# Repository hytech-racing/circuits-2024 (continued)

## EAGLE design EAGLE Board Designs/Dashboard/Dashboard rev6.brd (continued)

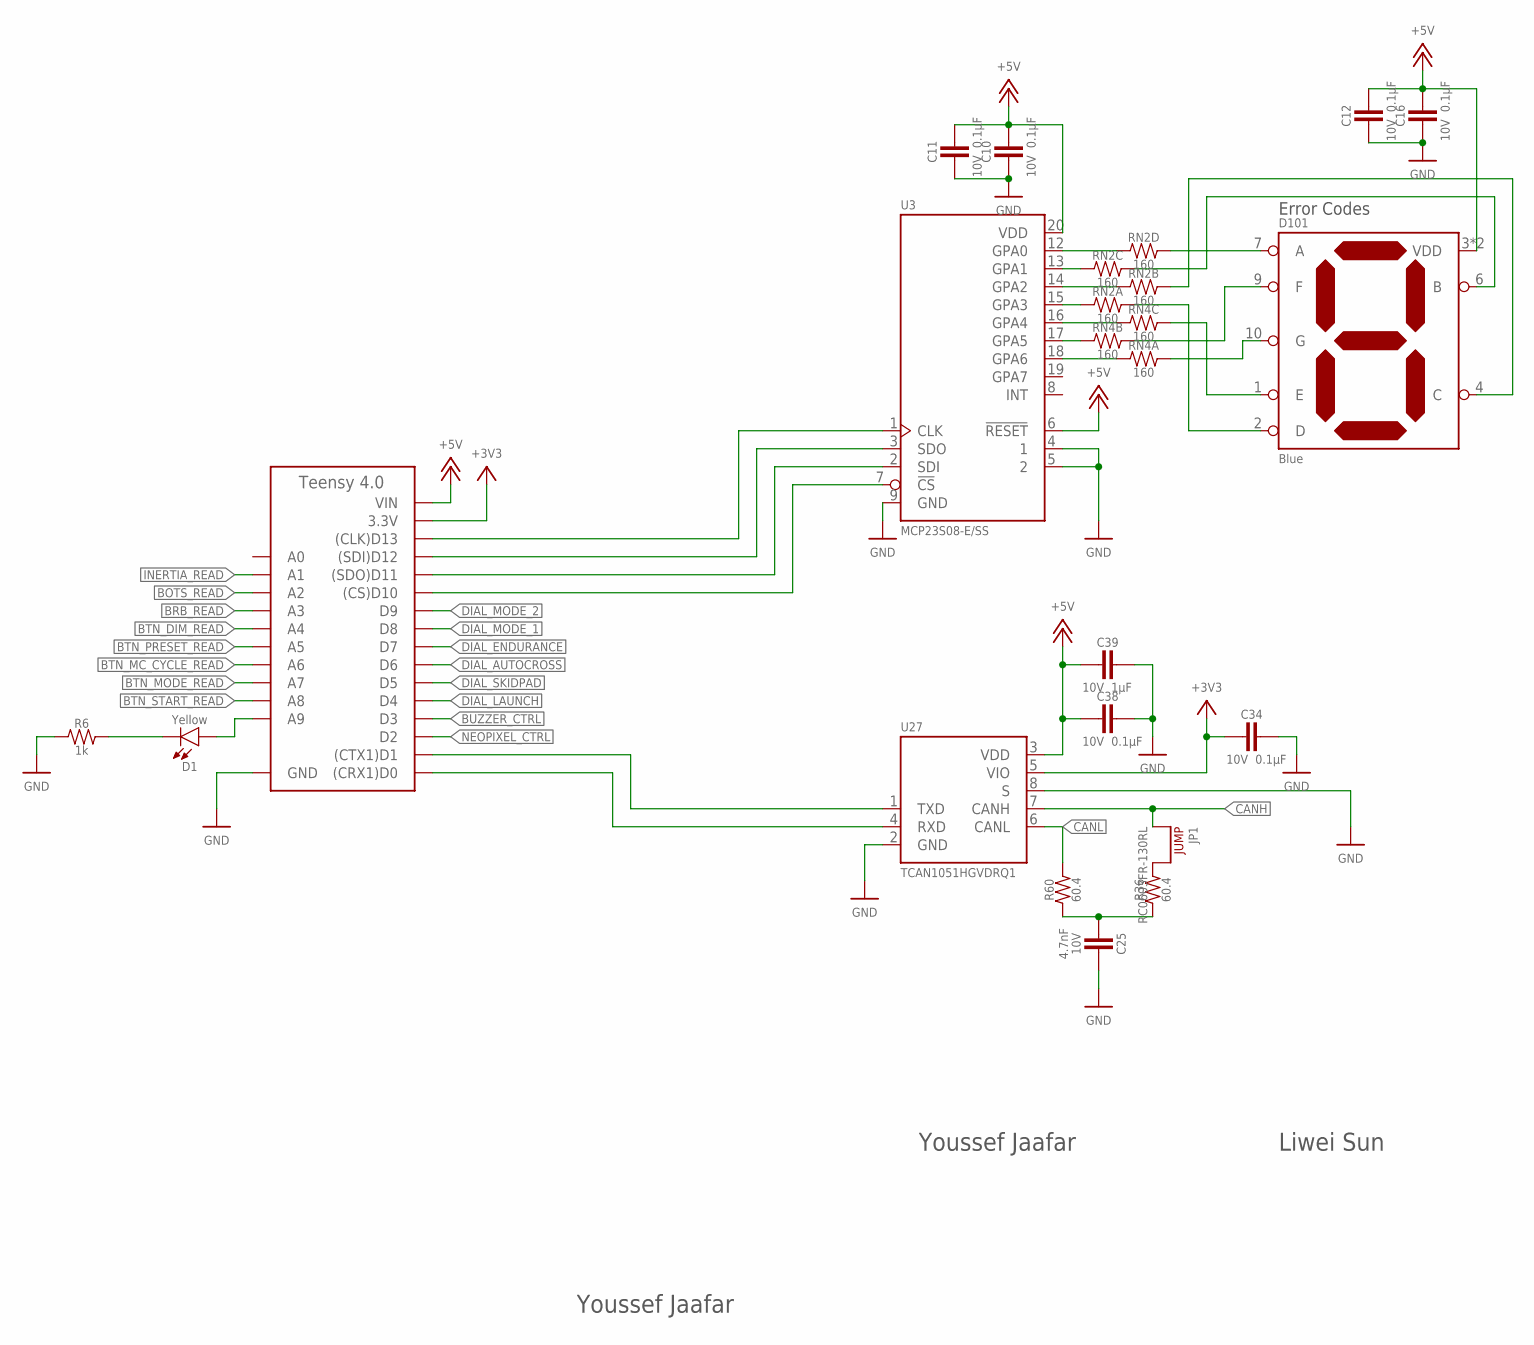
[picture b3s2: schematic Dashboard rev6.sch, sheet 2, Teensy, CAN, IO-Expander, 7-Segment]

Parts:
A2: TEENSY_4.0SM; TEENSY_SHORT_SSM
C10, C11, C12, C16, C34, C38: CAPACITOR_0603_10V_0.1UF; 0603-CAP
C25: CAPACITOR_0603_10V_4.7NF; 0603-CAP
C39: CAPACITOR_0603_10V_1UF; 0603-CAP
D1: LED_0603_YELLOW; 0603-LED
D101: LED_7_SEGMENT_BLUE_DSM7TA; DSM7T
JP1: JUMPER_0603_; 0603-RES
R6: RESISTOR_0603_1K; 0603-RES
R36, R60: RESISTOR_0603_60.4; 0603-RES
RN2, RN4: RESISTOR_NETWORK_4_160; 1206-RES-ARRAY
U3: MCP23S08; SSOP-20
U27: TCAN1051HQV-Q1; SOIC-08(NARROW,0.15")

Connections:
+3V3: A2.3.3V, C34.2, U27.5 (VIO); also elsewhere on the board
+5V: A2.VIN, C10.1, C11.1, C12.1, C16.1, C38.2, C39.2, D101.3 (VDD), D101.8 (VDD), U3.6 (!RESET), U3.20 (VDD), U27.3 (VDD); also elsewhere on the board
A: D101.7 (A), RN2.5 (2)
A2: RN2.4 (1), U3.12 (GPA0)
B: D101.6 (B), RN2.6 (2)
B2: RN2.3 (1), U3.13 (GPA1)
BOTS_READ: A2.D16 (A2); also elsewhere on the board
BRB_READ: A2.D17 (A3); also elsewhere on the board
BTN_DIM_READ: A2.D18 (A4); also elsewhere on the board
BTN_MC_CYCLE_READ: A2.D20 (A6); also elsewhere on the board
BTN_MODE_READ: A2.D21 (A7); also elsewhere on the board
BTN_PRESET_READ: A2.D19 (A5); also elsewhere on the board
BTN_START_READ: A2.D22 (A8); also elsewhere on the board
BUZZER_CTRL: A2.D3; also elsewhere on the board
C: D101.4 (C), RN2.7 (2)
C2: RN2.2 (1), U3.14 (GPA2)
CANH: JP1.1, U27.7 (CANH); also elsewhere on the board
CANL: R60.2, U27.6 (CANL); also elsewhere on the board
CIPO: A2.D12 ((SDI)D12), U3.3 (SDO)
CLK: A2.D13 ((CLK)D13), U3.1 (CLK)
COPI: A2.D11 ((SDO)D11), U3.2 (SDI)
CRX: A2.D0 ((CRX1)D0), U27.4 (RXD)
CS_CAN: A2.D10 ((CS)D10), U3.7 (!CS)
CTX: A2.D1 ((CTX1)D1), U27.1 (TXD)
D: D101.2 (D), RN2.8 (2)
D2: RN2.1, U3.15 (GPA3)
DIAL_AUTOCROSS: A2.D6; also elsewhere on the board
DIAL_ENDURANCE: A2.D7; also elsewhere on the board
DIAL_LAUNCH: A2.D4; also elsewhere on the board
DIAL_MODE_1: A2.D8; also elsewhere on the board
DIAL_MODE_2: A2.D9; also elsewhere on the board
DIAL_SKIDPAD: A2.D5; also elsewhere on the board
E: D101.1 (E), RN4.6 (2)
E2: RN4.3 (1), U3.16 (GPA4)
F: D101.9 (F), RN4.7 (2)
F2: RN4.2 (1), U3.17 (GPA5)
G: D101.10 (G), RN4.8 (2)
G2: RN4.1, U3.18 (GPA6)
GND: A2.AGND/GND (GND), A2.GND, C10.2, C11.2, C12.2, C16.2, C25.1, C34.1, C38.1, C39.1, R6.1, U3.4 (1), U3.5 (2), U3.9 (GND), U27.2 (GND), U27.8 (S); also elsewhere on the board
INERTIA_READ: A2.D15 (A1); also elsewhere on the board
unnamed: D1.1 (C), R6.2
unnamed: JP1.2, R36.2
unnamed: C25.2, R36.1, R60.1
NEOPIXEL_CTRL: A2.D2; also elsewhere on the board
TEENSY_ON: A2.D23 (A9), D1.2 (A)

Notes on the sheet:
Youssef Jaafar
Error Codes
Liwei Sun

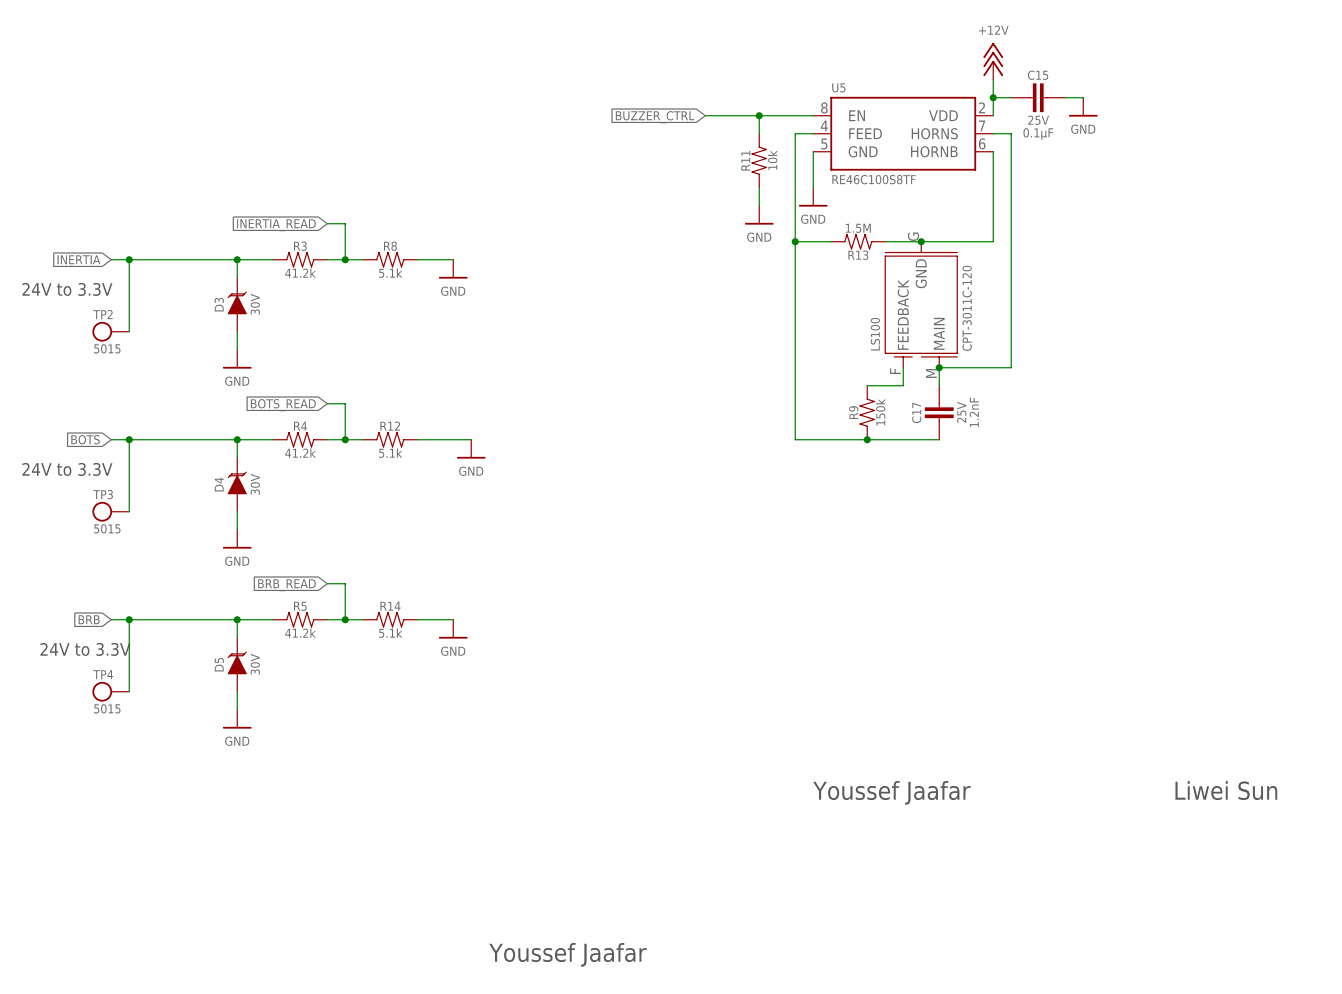
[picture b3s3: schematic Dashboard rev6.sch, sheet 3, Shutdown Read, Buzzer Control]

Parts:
C15: CAPACITOR_0603_25V_0.1UF; 0603-CAP
C17: CAPACITOR_0603_25V_1.2NF; 0603-CAP
D3, D4, D5: TVS_DO-214AA_30V; DO-214AA
LS100: BUZZER_3_PIN_CPT-3011C-120; CPT-3011C-120
R3, R4, R5: RESISTOR_0603_41.2K; 0603-RES
R8, R12, R14: RESISTOR_0603_5.1K; 0603-RES
R9: RESISTOR_0603_150K; 0603-RES
R11: RESISTOR_0603_10K; 0603-RES
R13: RESISTOR_0603_1.5M; 0603-RES
TP2, TP3, TP4: TEST_POINT; 5015
U5: RE46C100; SOIC-08(NARROW,0.15")

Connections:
+12V: C15.2, U5.2 (VDD); also elsewhere on the board
BOTS: D4.2 (C), R4.1, TP3.1; also elsewhere on the board
BOTS_READ: R4.2, R12.1; also elsewhere on the board
BRB: D5.2 (C), R5.1, TP4.1; also elsewhere on the board
BRB_READ: R5.2, R14.1; also elsewhere on the board
BUZZER_CTRL: R11.2, U5.8 (EN); also elsewhere on the board
FEED: C17.2, R9.1, R13.2, U5.4 (FEED)
GND: C15.1, D3.1 (A), D4.1 (A), D5.1 (A), R8.2, R11.1, R12.2, R14.2, U5.5 (GND); also elsewhere on the board
HORNB: LS100.G (GND), R13.1, U5.6 (HORNB)
HORNS: C17.1, LS100.M (MAIN), U5.7 (HORNS)
INERTIA: D3.2 (C), R3.1, TP2.1; also elsewhere on the board
INERTIA_READ: R3.2, R8.1; also elsewhere on the board
unnamed: LS100.F (FEEDBACK), R9.2

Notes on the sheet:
24V to 3.3V
Liwei Sun
Youssef Jaafar

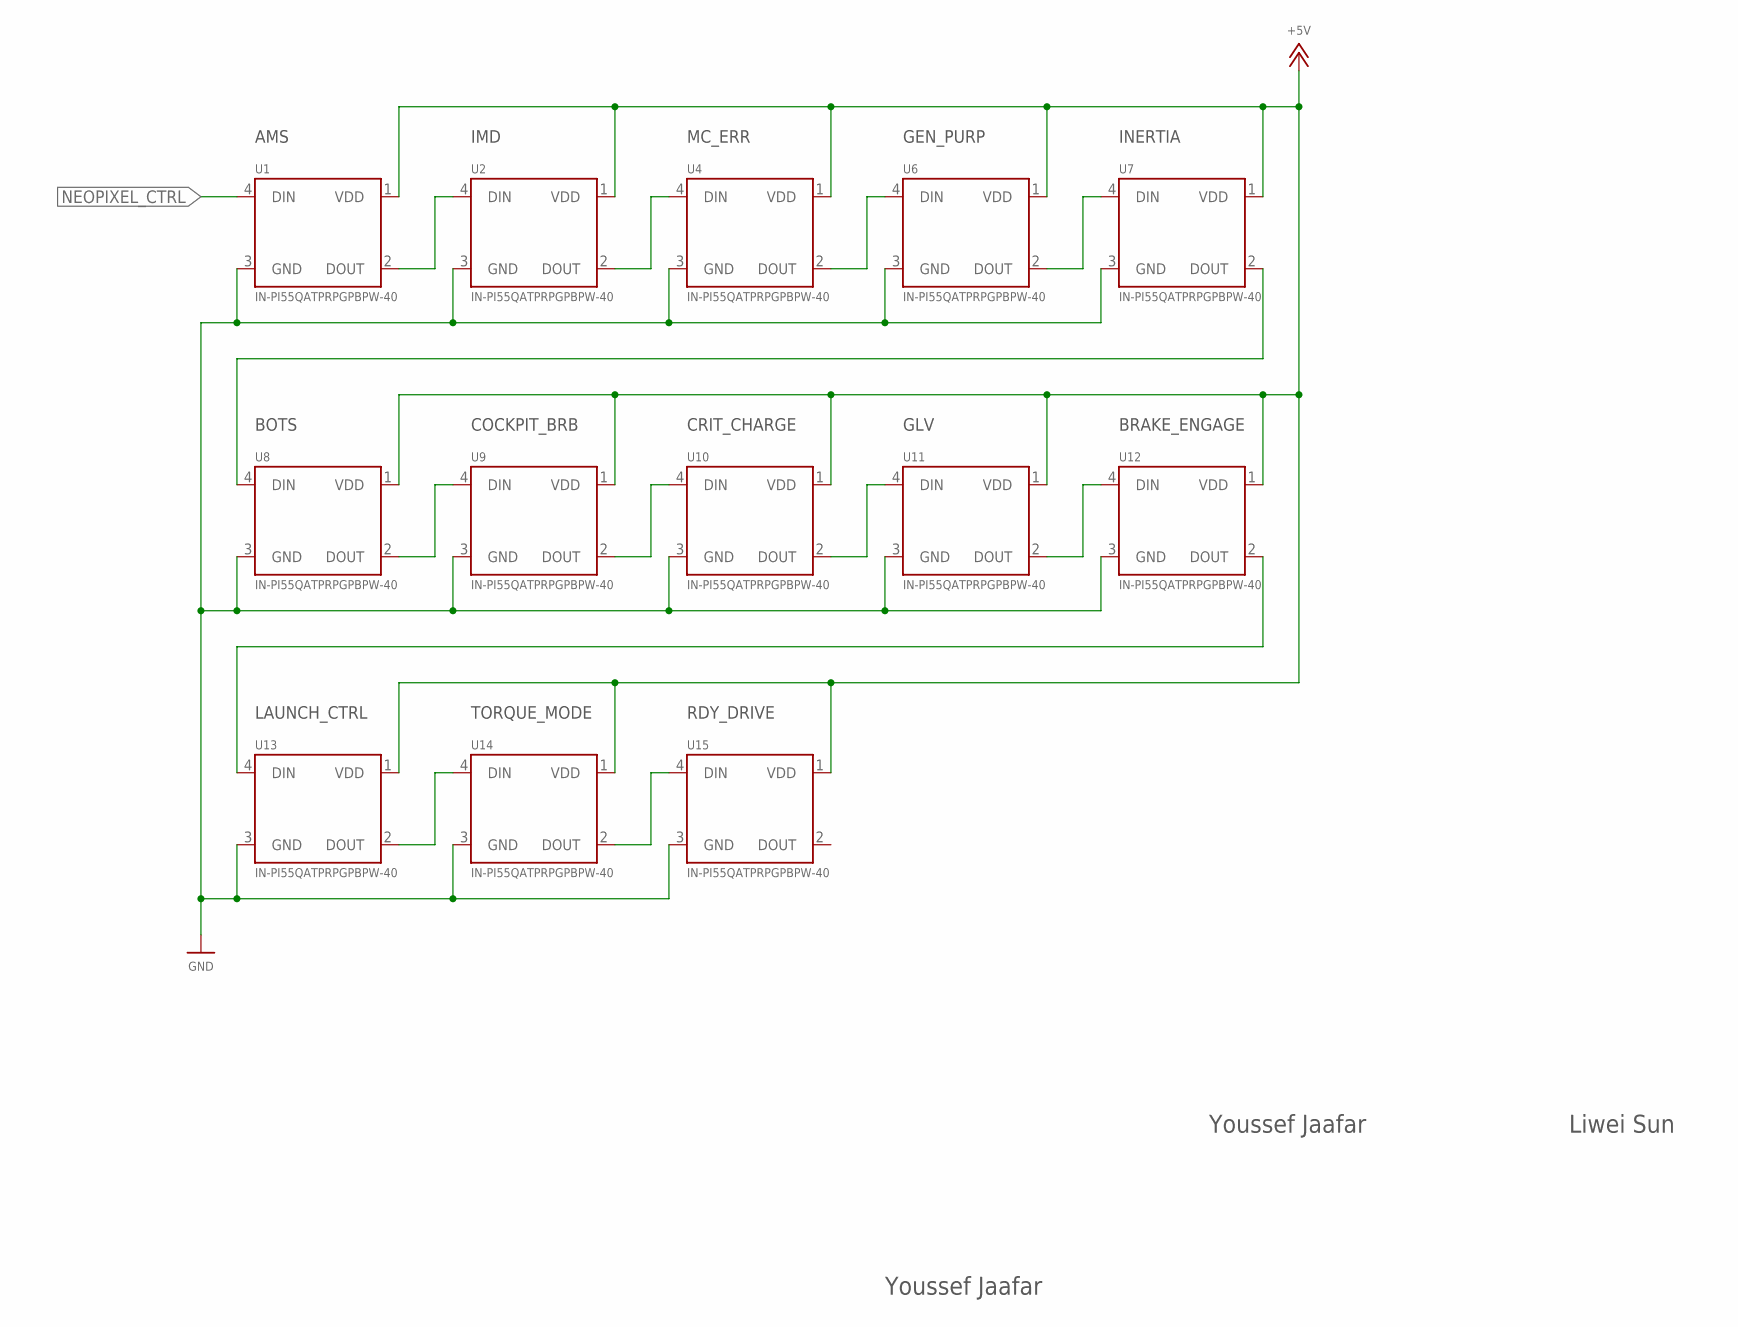
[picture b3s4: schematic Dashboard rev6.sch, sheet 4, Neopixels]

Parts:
U1, U2, U4, U6, U7, U8, U9, U10, U11, U12, U13, U14, U15: NEOPIXEL_IN-PI55QATPRPGPBPW-40; NEOPIXEL

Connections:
+5V: U1.1 (VDD), U2.1 (VDD), U4.1 (VDD), U6.1 (VDD), U7.1 (VDD), U8.1 (VDD), U9.1 (VDD), U10.1 (VDD), U11.1 (VDD), U12.1 (VDD), U13.1 (VDD), U14.1 (VDD), U15.1 (VDD); also elsewhere on the board
GND: U1.3 (GND), U2.3 (GND), U4.3 (GND), U6.3 (GND), U7.3 (GND), U8.3 (GND), U9.3 (GND), U10.3 (GND), U11.3 (GND), U12.3 (GND), U13.3 (GND), U14.3 (GND), U15.3 (GND); also elsewhere on the board
unnamed: U10.2 (DOUT), U11.4 (DIN)
unnamed: U8.2 (DOUT), U9.4 (DIN)
unnamed: U1.2 (DOUT), U2.4 (DIN)
unnamed: U2.2 (DOUT), U4.4 (DIN)
unnamed: U4.2 (DOUT), U6.4 (DIN)
unnamed: U6.2 (DOUT), U7.4 (DIN)
unnamed: U11.2 (DOUT), U12.4 (DIN)
unnamed: U14.2 (DOUT), U15.4 (DIN)
unnamed: U13.2 (DOUT), U14.4 (DIN)
unnamed: U9.2 (DOUT), U10.4 (DIN)
unnamed: U7.2 (DOUT), U8.4 (DIN)
unnamed: U12.2 (DOUT), U13.4 (DIN)
NEOPIXEL_CTRL: U1.4 (DIN); also elsewhere on the board

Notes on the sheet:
GEN_PURP
INERTIA
BOTS
COCKPIT_BRB
AMS
IMD
MC_ERR
CRIT_CHARGE
TORQUE_MODE
RDY_DRIVE
GLV
BRAKE_ENGAGE
LAUNCH_CTRL
Liwei Sun
Youssef Jaafar

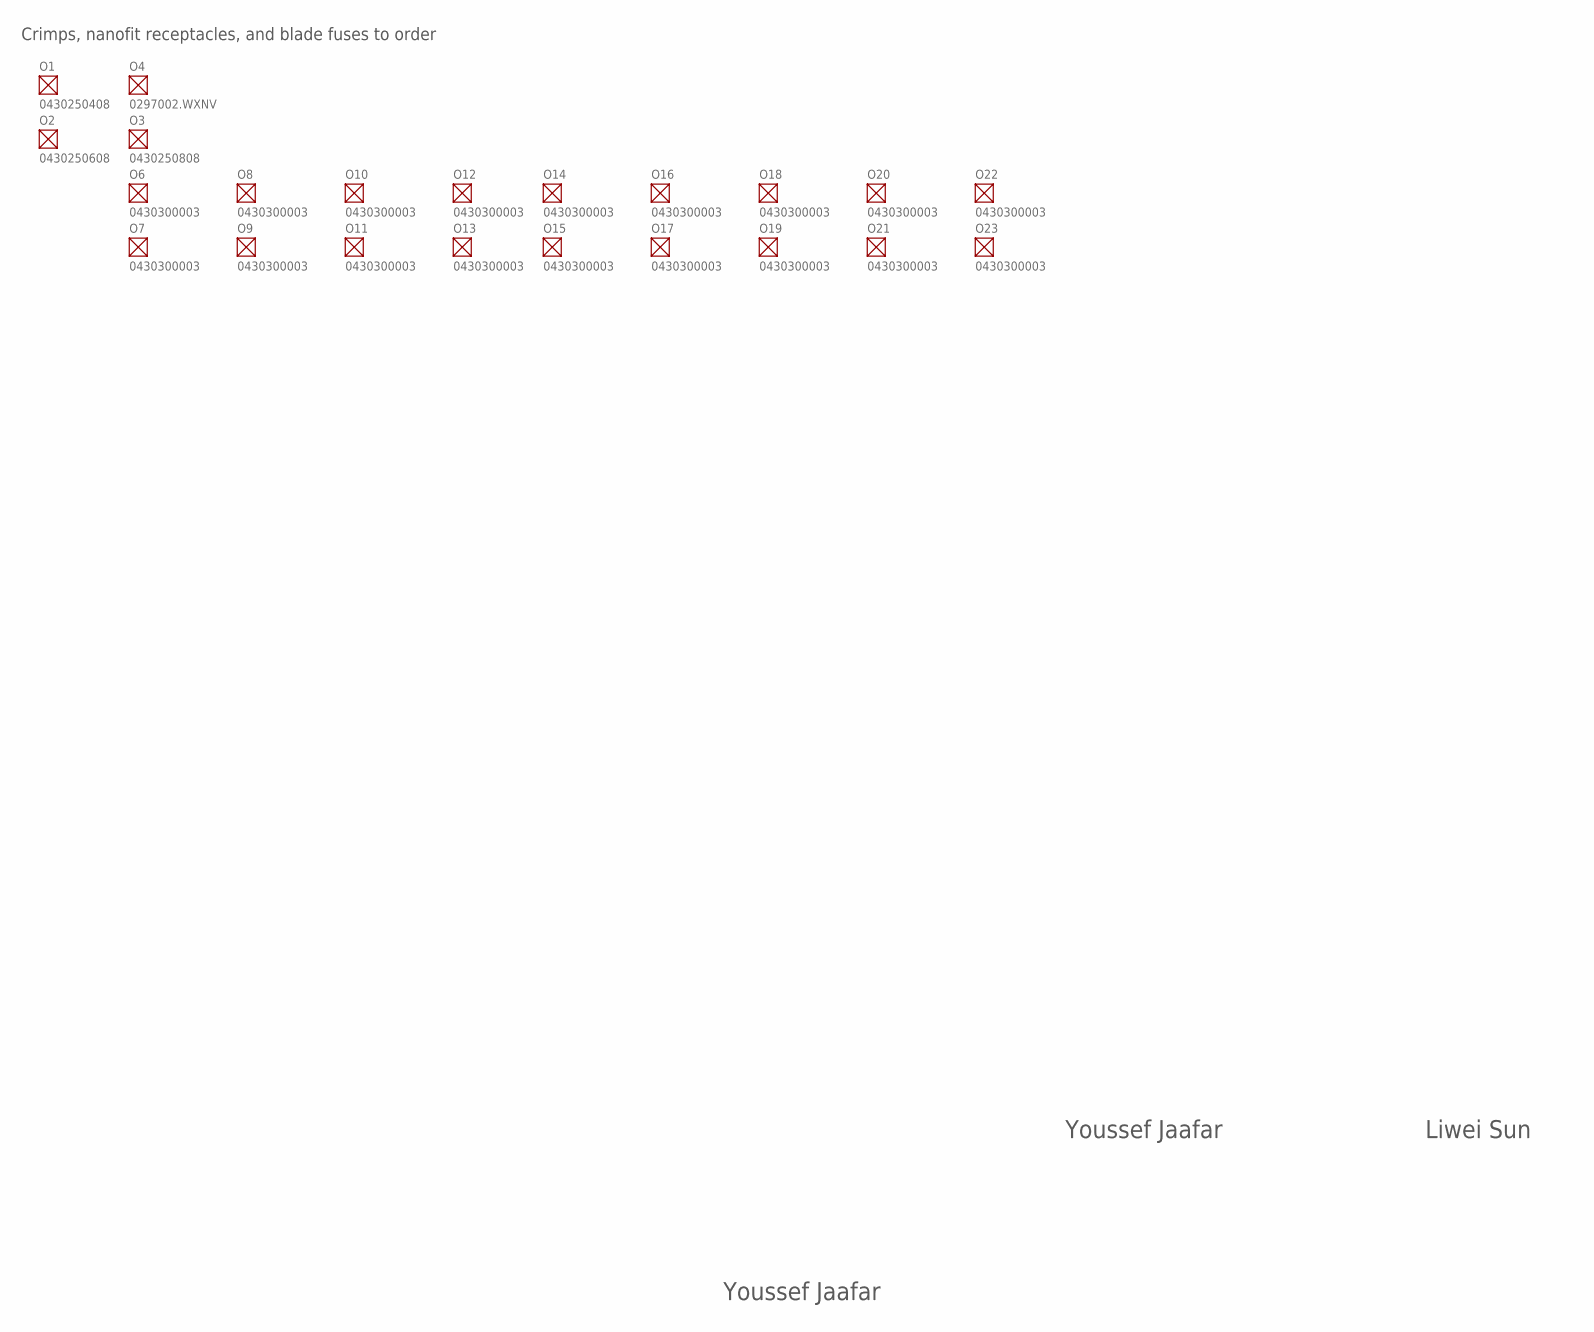
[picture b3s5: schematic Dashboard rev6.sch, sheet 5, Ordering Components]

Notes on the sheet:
Crimps, nanofit receptacles, and blade fuses to order
Liwei Sun
Youssef Jaafar

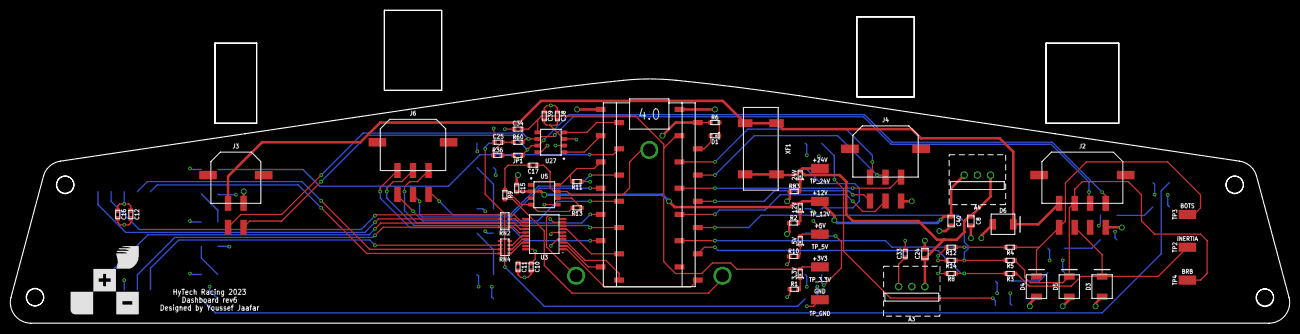
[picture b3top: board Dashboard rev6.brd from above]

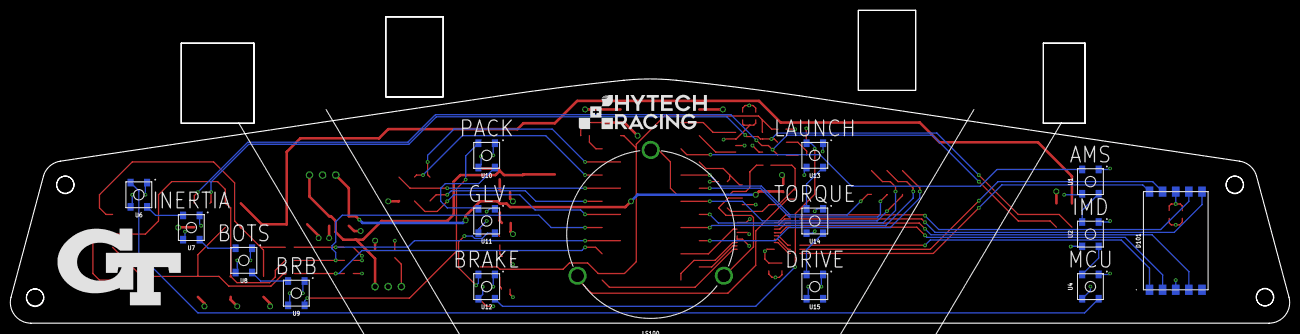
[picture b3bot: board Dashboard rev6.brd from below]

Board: 4 copper layers, 247.6 x 47.3 mm, 83 parts (17 on the bottom side), 71 nets.

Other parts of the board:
U$5: LOGO_GT_LARGE
U$6: LOGO_HYTECH_MEDIUM
U$7: LOGO_HYTECH_SQUARE_EXTRA_LARGE
U$8, U$9, U$10, U$11: MOUNTING_M3

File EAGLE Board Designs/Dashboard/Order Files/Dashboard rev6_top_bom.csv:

Comment,Designator,Footprint,LCSC Part #
CAPACITOR_0603_10V_0.1UF,C10 C11 C12 C16 C34 C38,0603-CAP,
CAPACITOR_0603_10V_1UF,C39,0603-CAP,
CAPACITOR_0603_10V_4.7NF,C25,0603-CAP,
CAPACITOR_0603_25V_0.1UF,C15,0603-CAP,
CAPACITOR_0603_25V_1.2NF,C17,0603-CAP,
CAPACITOR_0603_25V_10UF,C33,0603-CAP,
CAPACITOR_0805_50V_10UF,C8 C24 C40,0805-CAP,
CONNECTOR-6_μF_S_RA_,J4 J6,MOLEX_MICROFIT_SMD_RIGHTANGLE_06_DUAL,
CONNECTOR-8_μF_S_RA_,J2,MOLEX_MICROFIT_SMD_RIGHTANGLE_08_DUAL,
CONNECTOR-CAN_μF_S_RA_,J3,MOLEX_MICROFIT_SMD_RIGHTANGLE_04_DUAL,
FUSE_HOLDER_MINIBLADESMD,XF1,3588,
JUMPER_0603_,JP1,0603-RES,
LED_0603_BLUE,5V,0603-LED,
LED_0603_GREEN,3.3V,0603-LED,
LED_0603_ORANGE,24V,0603-LED,
LED_0603_RED,12V,0603-LED,
LED_0603_YELLOW,D1,0603-LED,
MCP23S08,U3,SSOP-20,
RE46C100,U5,SOIC-08(NARROW 0.15"),
RESISTOR_0603_1.5M,R13,0603-RES,
RESISTOR_0603_1K,R1 R2 R6 R10,0603-RES,
RESISTOR_0603_3.3K,R83,0603-RES,
RESISTOR_0603_5.1K,R8 R12 R14,0603-RES,
RESISTOR_0603_10K,R11,0603-RES,
RESISTOR_0603_41.2K,R3 R4 R5,0603-RES,
RESISTOR_0603_60.4,R36 R60,0603-RES,
RESISTOR_0603_150K,R9,0603-RES,
RESISTOR_NETWORK_4_160,RN2 RN4,1206-RES-ARRAY,
TCAN1051HQV-Q1,U27,SOIC-08(NARROW 0.15"),
TEENSY_4.0SM,A2,TEENSY_SHORT_SSM,
TEST_POINT,TP2 TP3 TP4 TP_3.3V TP_5V TP_12V TP_24V TP_GND,5015,
TVS_30VDO-214AA,D3 D4 D5 D6,DO-214AA,

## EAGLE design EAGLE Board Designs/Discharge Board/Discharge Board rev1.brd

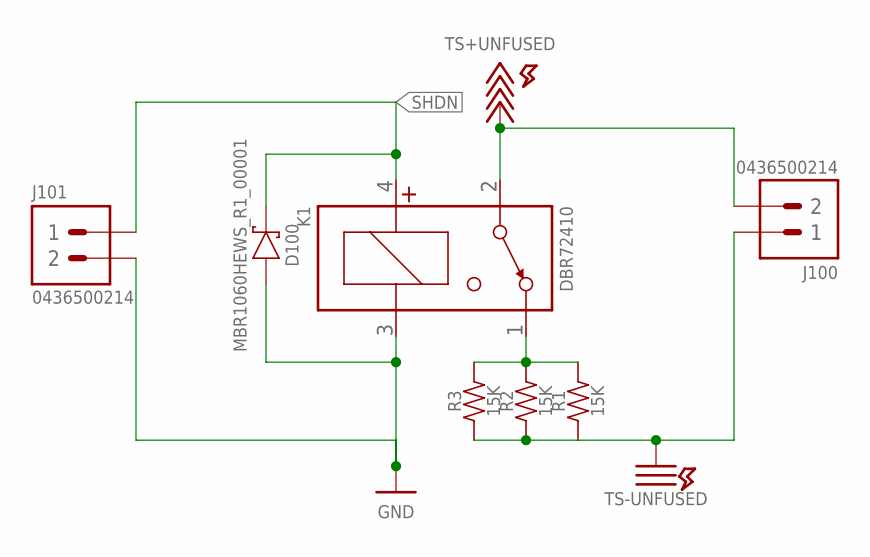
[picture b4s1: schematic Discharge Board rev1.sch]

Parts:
D100: SCHOTTKY_SOD323_60V; SOD-323
J100, J101: CONNECTOR-2_MICROFIT_SMD_RIGHTANGLE_02_SINGLE_BLA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; MOLEX_MICROFIT_SMD_RIGHTANGLE_02_SINGLE
K1: RELAY_SPST_NC_POLARIZED_D_24; D
R1, R2, R3: RESISTOR_B20-SHORTENED_15K; B20-SHORTENED

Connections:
GND: D100.A, J101.2, K1.3 (COIL-)
unnamed: K1.1 (CONTACT2), R1.2, R2.2, R3.2
SHDN: D100.C, J101.1, K1.4 (COIL+)
TS+UNFUSED: J100.2, K1.2 (CONTACT1)
TS-UNFUSED: J100.1, R1.1, R2.1, R3.1

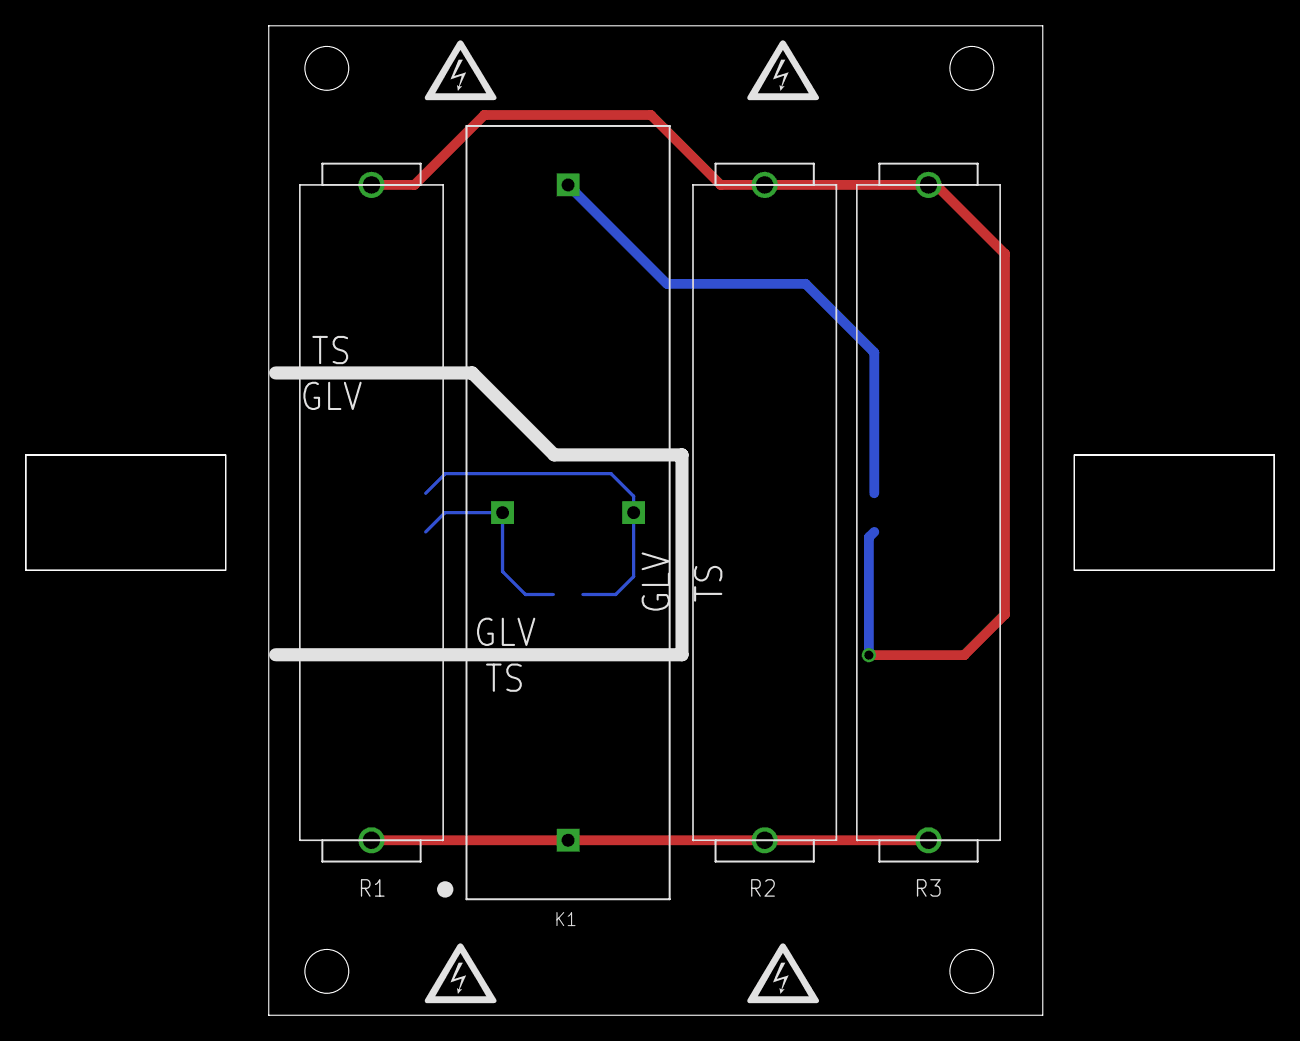
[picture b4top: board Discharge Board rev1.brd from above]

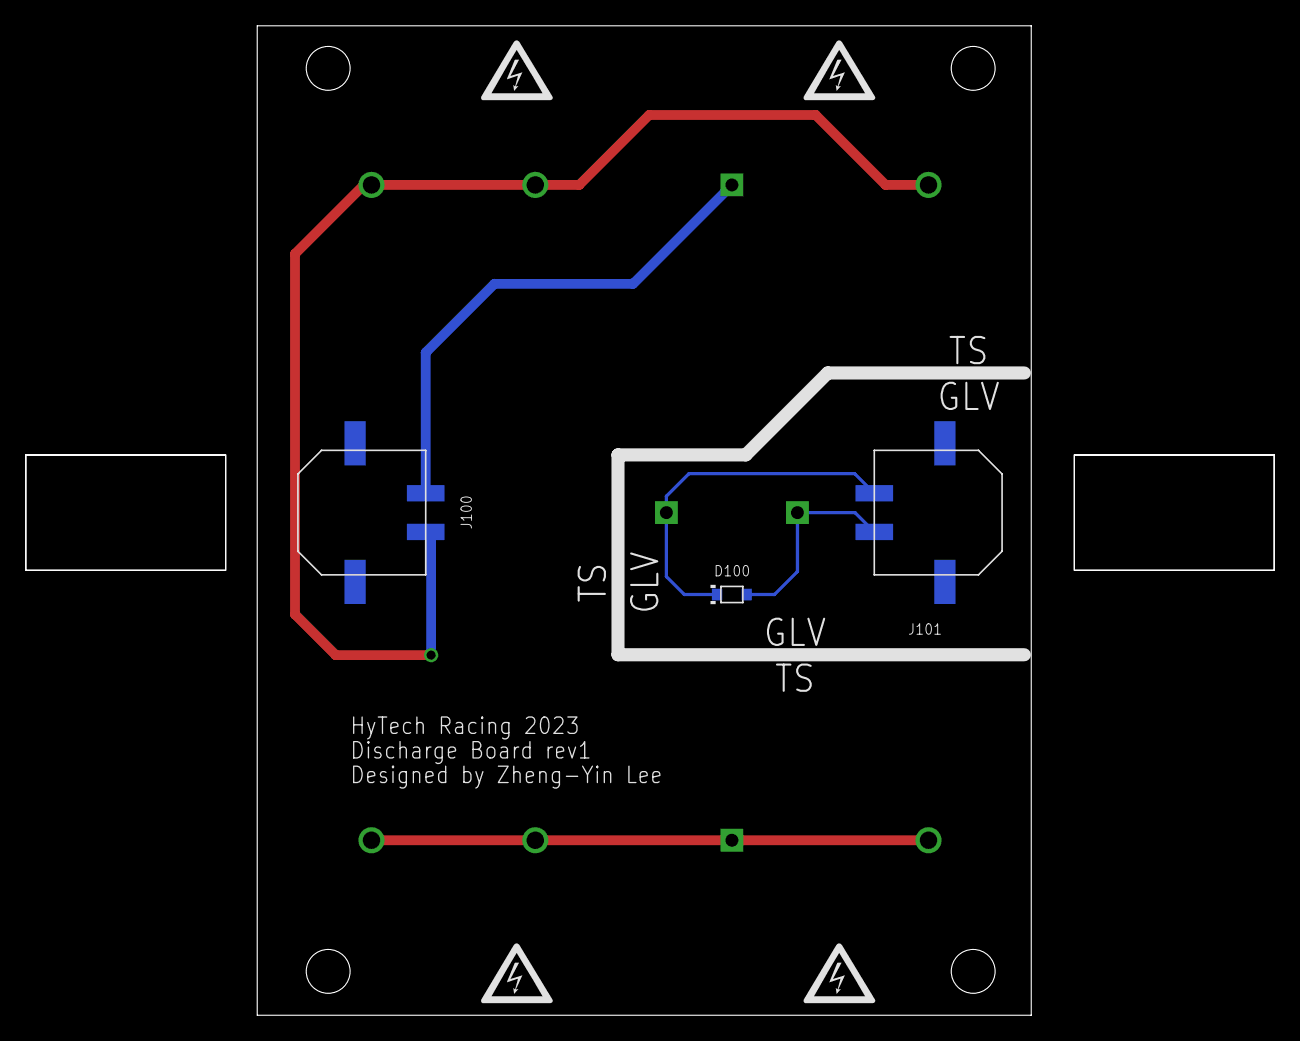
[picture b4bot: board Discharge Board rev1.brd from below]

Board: 2 copper layers, 60.0 x 76.7 mm, 25 parts (7 on the bottom side), 5 nets.

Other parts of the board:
U$1, U$2, U$5: GLV
U$3, U$4, U$6: TS
U$7, U$8, U$9, U$10, U$11, U$12, U$13, U$14: HV_MEDIUM
U$15, U$16, U$17, U$18: MOUNTING_M3

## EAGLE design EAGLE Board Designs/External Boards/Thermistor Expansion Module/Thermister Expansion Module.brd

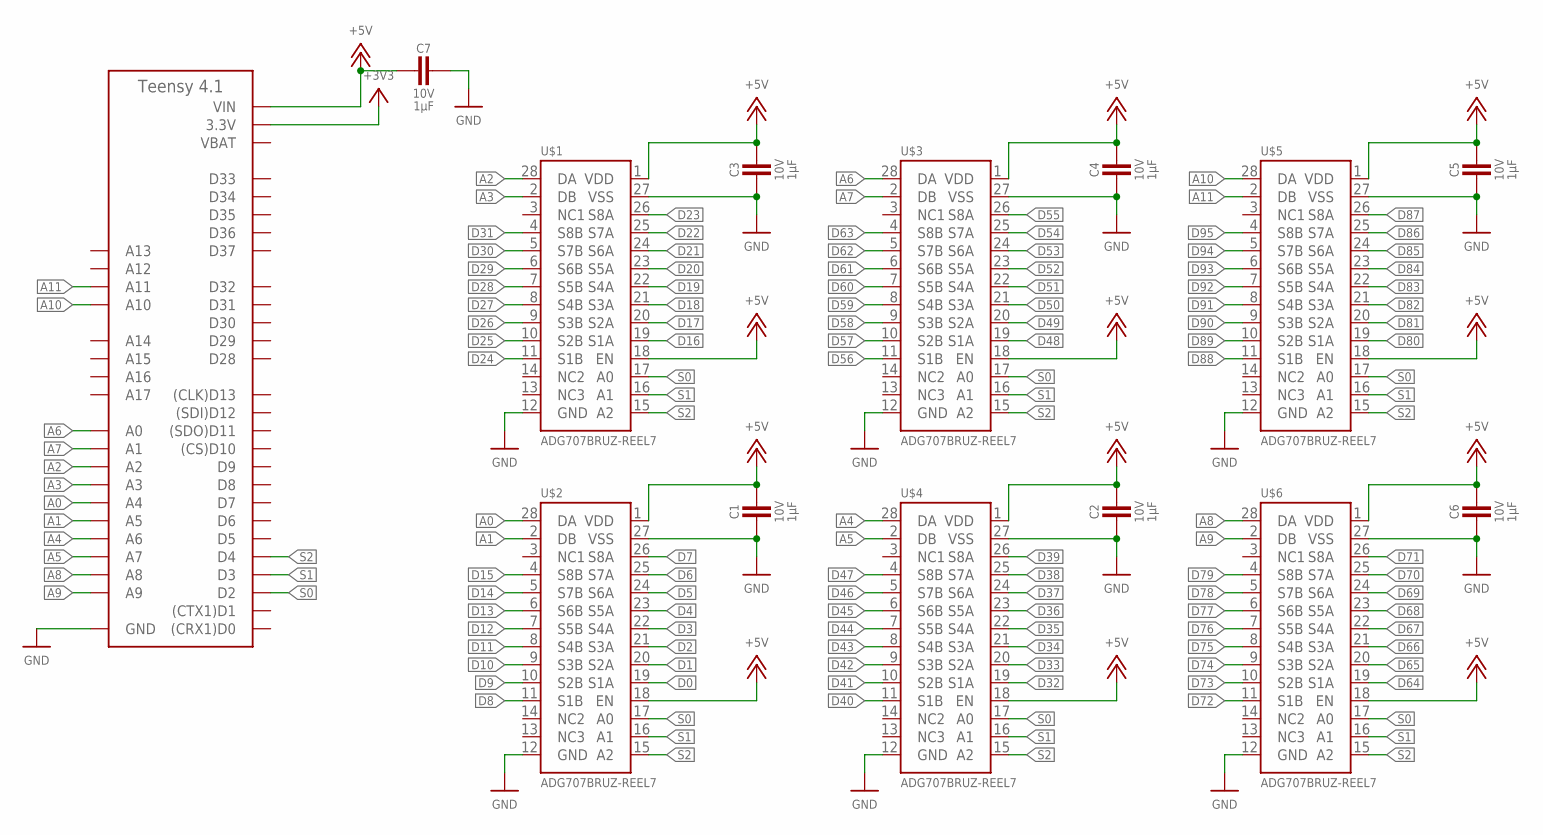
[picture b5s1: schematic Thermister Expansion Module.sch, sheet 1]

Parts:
A1: TEENSY_4.1; TEENSY_LONG_EXT
C1, C2, C3, C4, C5, C6, C7: CAPACITOR_0603_10V_1UF; 0603-CAP
U$1, U$2, U$3, U$4, U$5, U$6: ADG707; TSSOP-28

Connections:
+3V3: A1.3V3 (3.3V), A1.3V3@2 (3.3V), A1.3V3@3 (3.3V); also elsewhere on the board
+5V: A1.VIN, C1.1, C2.1, C3.1, C4.1, C5.1, C6.1, C7.2, U$1.1 (VDD), U$1.18 (EN), U$2.1 (VDD), U$2.18 (EN), U$3.1 (VDD), U$3.18 (EN), U$4.1 (VDD), U$4.18 (EN), U$5.1 (VDD), U$5.18 (EN), U$6.1 (VDD), U$6.18 (EN); also elsewhere on the board
A0: A1.D18 (A4), U$2.28 (DA)
A1: A1.D19 (A5), U$2.2 (DB)
A2: A1.D16 (A2), U$1.28 (DA)
A3: A1.D17 (A3), U$1.2 (DB)
A4: A1.D20 (A6), U$4.28 (DA)
A5: A1.D21 (A7), U$4.2 (DB)
A6: A1.D14 (A0), U$3.28 (DA)
A7: A1.D15 (A1), U$3.2 (DB)
A8: A1.D22 (A8), U$6.28 (DA)
A9: A1.D23 (A9), U$6.2 (DB)
A10: A1.D24 (A10), U$5.28 (DA)
A11: A1.D25 (A11), U$5.2 (DB)
D0: U$2.19 (S1A); also elsewhere on the board
D1: U$2.20 (S2A); also elsewhere on the board
D2: U$2.21 (S3A); also elsewhere on the board
D3: U$2.22 (S4A); also elsewhere on the board
D4: U$2.23 (S5A); also elsewhere on the board
D5: U$2.24 (S6A); also elsewhere on the board
D6: U$2.25 (S7A); also elsewhere on the board
D7: U$2.26 (S8A); also elsewhere on the board
D8: U$2.11 (S1B); also elsewhere on the board
D9: U$2.10 (S2B); also elsewhere on the board
D10: U$2.9 (S3B); also elsewhere on the board
D11: U$2.8 (S4B); also elsewhere on the board
D12: U$2.7 (S5B); also elsewhere on the board
D13: U$2.6 (S6B); also elsewhere on the board
D14: U$2.5 (S7B); also elsewhere on the board
D15: U$2.4 (S8B); also elsewhere on the board
D16: U$1.19 (S1A); also elsewhere on the board
D17: U$1.20 (S2A); also elsewhere on the board
D18: U$1.21 (S3A); also elsewhere on the board
D19: U$1.22 (S4A); also elsewhere on the board
D20: U$1.23 (S5A); also elsewhere on the board
D21: U$1.24 (S6A); also elsewhere on the board
D22: U$1.25 (S7A); also elsewhere on the board
D23: U$1.26 (S8A); also elsewhere on the board
D24: U$1.11 (S1B); also elsewhere on the board
D25: U$1.10 (S2B); also elsewhere on the board
D26: U$1.9 (S3B); also elsewhere on the board
D27: U$1.8 (S4B); also elsewhere on the board
D28: U$1.7 (S5B); also elsewhere on the board
D29: U$1.6 (S6B); also elsewhere on the board
D30: U$1.5 (S7B); also elsewhere on the board
D31: U$1.4 (S8B); also elsewhere on the board
D32: U$4.19 (S1A); also elsewhere on the board
D33: U$4.20 (S2A); also elsewhere on the board
D34: U$4.21 (S3A); also elsewhere on the board
D35: U$4.22 (S4A); also elsewhere on the board
D36: U$4.23 (S5A); also elsewhere on the board
D37: U$4.24 (S6A); also elsewhere on the board
D38: U$4.25 (S7A); also elsewhere on the board
D39: U$4.26 (S8A); also elsewhere on the board
D40: U$4.11 (S1B); also elsewhere on the board
D41: U$4.10 (S2B); also elsewhere on the board
D42: U$4.9 (S3B); also elsewhere on the board
D43: U$4.8 (S4B); also elsewhere on the board
D44: U$4.7 (S5B); also elsewhere on the board
D45: U$4.6 (S6B); also elsewhere on the board
D46: U$4.5 (S7B); also elsewhere on the board
D47: U$4.4 (S8B); also elsewhere on the board
D48: U$3.19 (S1A); also elsewhere on the board
D49: U$3.20 (S2A); also elsewhere on the board
D50: U$3.21 (S3A); also elsewhere on the board
D51: U$3.22 (S4A); also elsewhere on the board
D52: U$3.23 (S5A); also elsewhere on the board
D53: U$3.24 (S6A); also elsewhere on the board
D54: U$3.25 (S7A); also elsewhere on the board
D55: U$3.26 (S8A); also elsewhere on the board
D56: U$3.11 (S1B); also elsewhere on the board
D57: U$3.10 (S2B); also elsewhere on the board
D58: U$3.9 (S3B); also elsewhere on the board
D59: U$3.8 (S4B); also elsewhere on the board
D60: U$3.7 (S5B); also elsewhere on the board
D61: U$3.6 (S6B); also elsewhere on the board
D62: U$3.5 (S7B); also elsewhere on the board
D63: U$3.4 (S8B); also elsewhere on the board
D64: U$6.19 (S1A); also elsewhere on the board
D65: U$6.20 (S2A); also elsewhere on the board
D66: U$6.21 (S3A); also elsewhere on the board
D67: U$6.22 (S4A); also elsewhere on the board
D68: U$6.23 (S5A); also elsewhere on the board
D69: U$6.24 (S6A); also elsewhere on the board
D70: U$6.25 (S7A); also elsewhere on the board
D71: U$6.26 (S8A); also elsewhere on the board
D72: U$6.11 (S1B); also elsewhere on the board
D73: U$6.10 (S2B); also elsewhere on the board
D74: U$6.9 (S3B); also elsewhere on the board
D75: U$6.8 (S4B); also elsewhere on the board
D76: U$6.7 (S5B); also elsewhere on the board
D77: U$6.6 (S6B); also elsewhere on the board
D78: U$6.5 (S7B); also elsewhere on the board
D79: U$6.4 (S8B); also elsewhere on the board
D80: U$5.19 (S1A); also elsewhere on the board
D81: U$5.20 (S2A); also elsewhere on the board
D82: U$5.21 (S3A); also elsewhere on the board
D83: U$5.22 (S4A); also elsewhere on the board
D84: U$5.23 (S5A); also elsewhere on the board
D85: U$5.24 (S6A); also elsewhere on the board
D86: U$5.25 (S7A); also elsewhere on the board
D87: U$5.26 (S8A); also elsewhere on the board
D88: U$5.11 (S1B); also elsewhere on the board
D89: U$5.10 (S2B); also elsewhere on the board
D90: U$5.9 (S3B); also elsewhere on the board
D91: U$5.8 (S4B); also elsewhere on the board
D92: U$5.7 (S5B); also elsewhere on the board
D93: U$5.6 (S6B); also elsewhere on the board
D94: U$5.5 (S7B); also elsewhere on the board
D95: U$5.4 (S8B); also elsewhere on the board
GND: A1.AGND/GND (GND), A1.GND, A1.GND@2 (GND), C1.2, C2.2, C3.2, C4.2, C5.2, C6.2, C7.1, U$1.12 (GND), U$1.27 (VSS), U$2.12 (GND), U$2.27 (VSS), U$3.12 (GND), U$3.27 (VSS), U$4.12 (GND), U$4.27 (VSS), U$5.12 (GND), U$5.27 (VSS), U$6.12 (GND), U$6.27 (VSS); also elsewhere on the board
S0: A1.D2, U$1.17 (A0), U$2.17 (A0), U$3.17 (A0), U$4.17 (A0), U$5.17 (A0), U$6.17 (A0)
S1: A1.D3, U$1.16 (A1), U$2.16 (A1), U$3.16 (A1), U$4.16 (A1), U$5.16 (A1), U$6.16 (A1)
S2: A1.D4, U$1.15 (A2), U$2.15 (A2), U$3.15 (A2), U$4.15 (A2), U$5.15 (A2), U$6.15 (A2)
VBAT: A1.VBAT
